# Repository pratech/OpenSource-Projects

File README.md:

# OpenSource-Projects
Open Source Pinwheel Robotics Project
Pinwheel Robotics is a company based in Bengaluru , Karnataka ,India
Our aim is to make programming and Robotics fun for students 
This will foster more creativity among kids.
At Pinwheel we believe Education should have no boundary and hence creating this open source projects hub.
Please contact us at admin@pinwheel.in
Alternate Email address of founder - prateek.ideafires@gmail.com
Our Tech blogs are at www.pinwheel.in
Facebook- www.facebook.com/pinwheeler
Instagram- www.instagram.com/pinwheelrobotics
Youtube - Search for Pinwheel Robotics .

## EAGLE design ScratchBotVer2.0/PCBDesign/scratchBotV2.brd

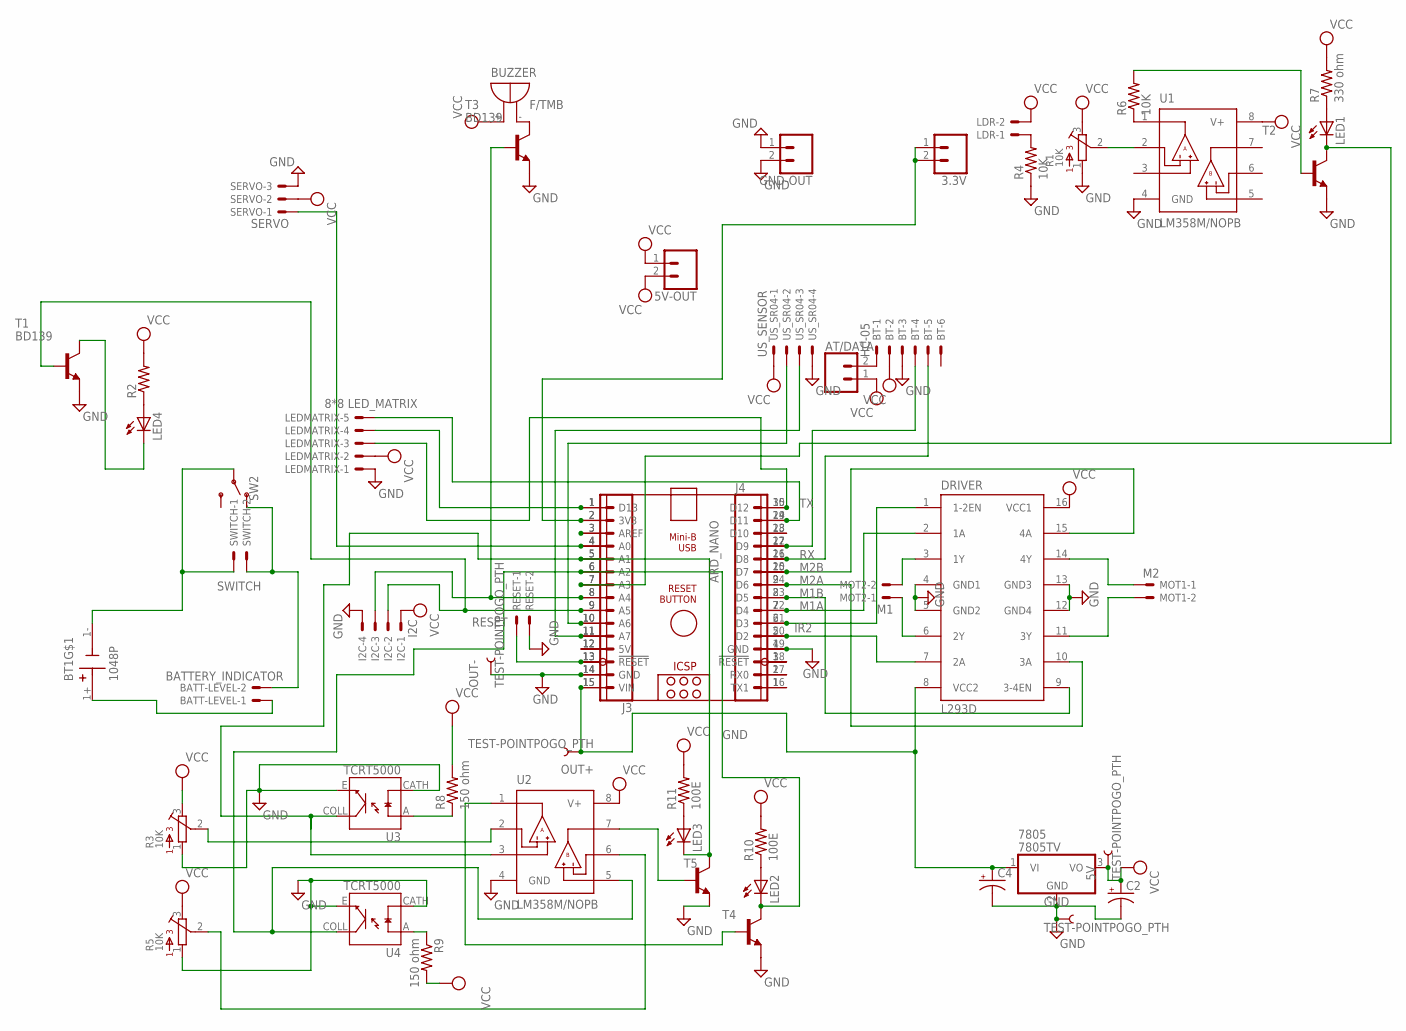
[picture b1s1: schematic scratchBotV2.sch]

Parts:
3.3V, 5V-OUT: CONN_02; 1X02
5V: TEST-POINTPOGO_PTH; 1X01_NO_SILK
7805: 7805TV; TO220V
ARD_NANO: ARDUINO_NANO
AT/DATA: CONN_02; 1X02
BATT-LEVEL: BATTERY_INDICATOR; JST-XH-02-PACKAGE-LONG-PAD
BT: HC-05; JST-XH-06-PACKAGE-LONG-PAD
BT1: 1048P; BAT_1048P
BUZZER: F/TMB
C2, C4: CPOL-USE2.5-5; E2,5-5
DRIVER: L293D; DIL16
GND: TEST-POINTPOGO_PTH; 1X01_NO_SILK
GND-OUT: CONN_02; 1X02
I2C: I2C; JST-XH-04-PACKAGE-LONG-PAD
J3, J4: CONN_15; 1X15
LDR: JST-XH-02-PIN-LONG-PAD; JST-XH-02-PACKAGE-LONG-PAD
LED1, LED2, LED3, LED4: LEDCHIPLED_1206; CHIPLED_1206
LEDMATRIX: 8*8 LED_MATRIX; JST-XH-05-PACKAGE-LONG-PAD
MOT1: M2; JST-XH-02-PACKAGE-LONG-PAD
MOT2: M1; JST-XH-02-PACKAGE-LONG-PAD
OUT+: TEST-POINTPOGO_PTH; 1X01_NO_SILK
OUT-: TEST-POINTPOGO_PTH; 1X01_NO_SILK
R1, R3, R5: 10K; 3362H
R2: R-US_0204/7; 0204/7
R4, R6: 10K; M1206
R7: 330 ohm; M1206
R8, R9: 150 ohm; M1206
R10, R11: 100E; M1206
RESET: RESET; JST-XH-02-PACKAGE-LONG-PAD
SERVO: SERVO; JST-XH-03-PACKAGE-LONG-PAD
SW2: SWITCH-SPDT-PTH-11.6X4.0MM; SWITCH_SPDT_PTH_11.6X4.0MM
SWITCH: SWITCH; JST-XH-02-PACKAGE-LONG-PAD
T1, T3: BD139; TO126
T2, T4, T5: -NPN-SOT23-EBC; SOT23-EBC
U1, U2: LM358M/NOPB; SOIC127P599X175-8N
U3, U4: TCRT5000; OPTO_TCRT5000
US_SR04: US_SENSOR; JST-XH-04-PACKAGE-LONG-PAD

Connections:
9V-MT3608: 7805.1 (VI), ARD_NANO.15 (VIN), C4.+, DRIVER.8 (VCC2), J3.15, OUT+.1
ECHO: ARD_NANO.8 (A4), I2C.3, J3.8, T3.3 (B)
GND: 7805.2 (GND), ARD_NANO.14 (GND), ARD_NANO.19 (GND), BT.3, C2.-, C4.-, DRIVER.4 (GND1), DRIVER.5 (GND2), DRIVER.12 (GND4), DRIVER.13 (GND3), GND.1, GND-OUT.1, GND-OUT.2, I2C.4, J3.14, J4.4, LEDMATRIX.1, OUT-.1, R1.1, R3.1, R4.1, R5.1, RESET.2, SERVO.3, T1.1 (E), T2.E, T3.1 (E), T4.E, T5.E, U1.4 (GND), U2.4 (GND), U3.CATH, U3.E, U4.CATH, U4.E, US_SR04.4
IR2: ARD_NANO.21 (D3), DRIVER.1 (1-2EN), J4.6
M1A: ARD_NANO.22 (D4), DRIVER.2 (1A), J4.7
M1B: ARD_NANO.23 (D5), DRIVER.9 (3-4EN), J4.8
M2A: ARD_NANO.24 (D6), DRIVER.10 (3A), J4.9
M2B: ARD_NANO.25 (D7), DRIVER.15 (4A), J4.10
unnamed: BT1.1-, SW2.2, SWITCH.1
unnamed: DRIVER.3 (1Y), MOT2.2
unnamed: R1.2, U1.2 (-INA)
unnamed: DRIVER.6 (2Y), MOT2.1
unnamed: ARD_NANO.4 (A0), J3.4, SERVO.1
unnamed: BATT-LEVEL.1, BT1.1+
unnamed: ARD_NANO.10 (A6), J3.10, US_SR04.2
unnamed: DRIVER.14 (4Y), MOT1.1
unnamed: ARD_NANO.28 (D10), J4.13
unnamed: DRIVER.11 (3Y), MOT1.2
unnamed: ARD_NANO.27 (D9), BT.4, J4.12
unnamed: ARD_NANO.1 (D13), J3.1, LEDMATRIX.4
unnamed: ARD_NANO.7 (A3), J3.7, LED1.C, T2.C
unnamed: ARD_NANO.5 (A1), J3.5, LED3.C, T5.C, U2.3 (+INA), U3.COLL
unnamed: LED4.C, T1.2 (C)
unnamed: BATT-LEVEL.2, SW2.1 (O), SWITCH.2
unnamed: ARD_NANO.13 (!RESET), J3.13, RESET.1
unnamed: 3.3V.1, 3.3V.2, ARD_NANO.2 (3V3), J3.2
unnamed: ARD_NANO.11 (A7), J3.11, US_SR04.3
unnamed: ARD_NANO.3 (AREF), J3.3
unnamed: ARD_NANO.9 (A5), I2C.2, J3.9, T1.3 (B)
unnamed: R8.1, U3.A
unnamed: ARD_NANO.12 (5V), J3.12
unnamed: LDR.1, R4.2
unnamed: R6.1, U1.1 (OUTA)
unnamed: R9.1, U4.A
unnamed: BUZZER.-, T3.2 (C)
unnamed: R6.2, T2.B
unnamed: ARD_NANO.6 (A2), J3.6, LED2.C, T4.C, U2.5 (+INB), U4.COLL
unnamed: ARD_NANO.29 (D11), J4.14, LEDMATRIX.5
unnamed: ARD_NANO.16 (TX1), J4.1
unnamed: ARD_NANO.17 (RX0), J4.2
unnamed: ARD_NANO.18 (!RESET), J4.3
unnamed: AT/DATA.2, BT.1
unnamed: LED1.A, R7.1
unnamed: ARD_NANO.20 (D2), DRIVER.7 (2A), J4.5
unnamed: R3.2, U2.2 (-INA)
unnamed: LED3.A, R11.1
unnamed: LED2.A, R10.1
unnamed: T4.B, U2.1 (OUTA)
unnamed: T5.B, U2.7 (OUTB)
unnamed: R5.2, U2.6 (-INB)
unnamed: LED4.A, R2.1
RX: ARD_NANO.26 (D8), BT.5, J4.11
TX: ARD_NANO.30 (D12), J4.15, LEDMATRIX.3
VCC: 5V.1, 5V-OUT.1, 5V-OUT.2, 7805.3 (VO), AT/DATA.1, BT.2, BUZZER.+, C2.+, DRIVER.16 (VCC1), I2C.1, LDR.2, LEDMATRIX.2, R1.3, R2.2, R3.3, R5.3, R7.2, R8.2, R9.2, R10.2, R11.2, SERVO.2, U1.8 (V+), U2.8 (V+), US_SR04.1

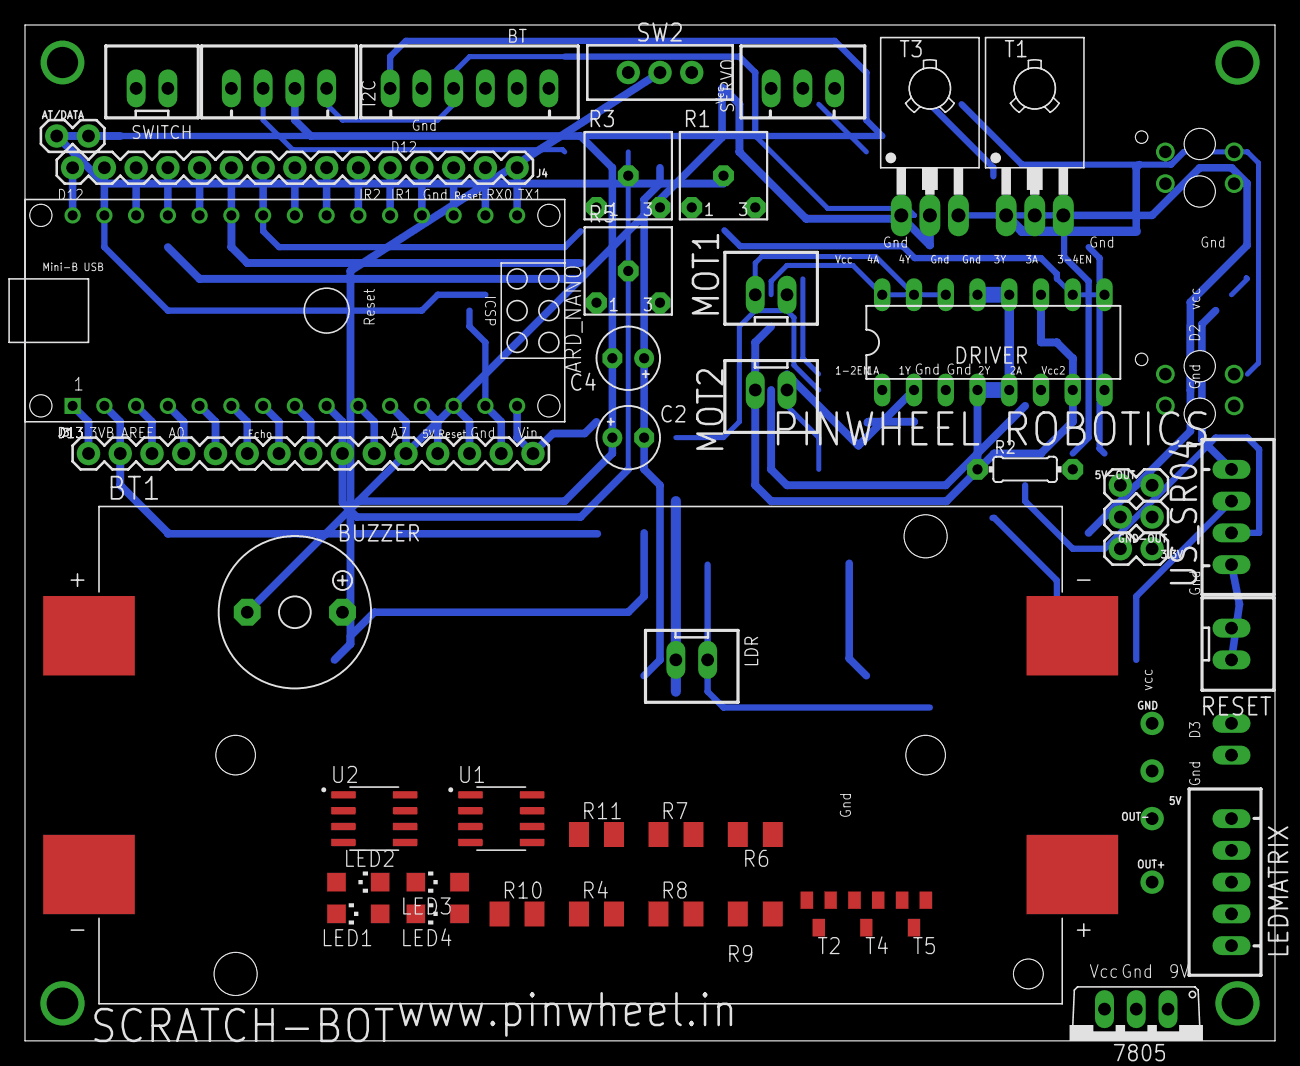
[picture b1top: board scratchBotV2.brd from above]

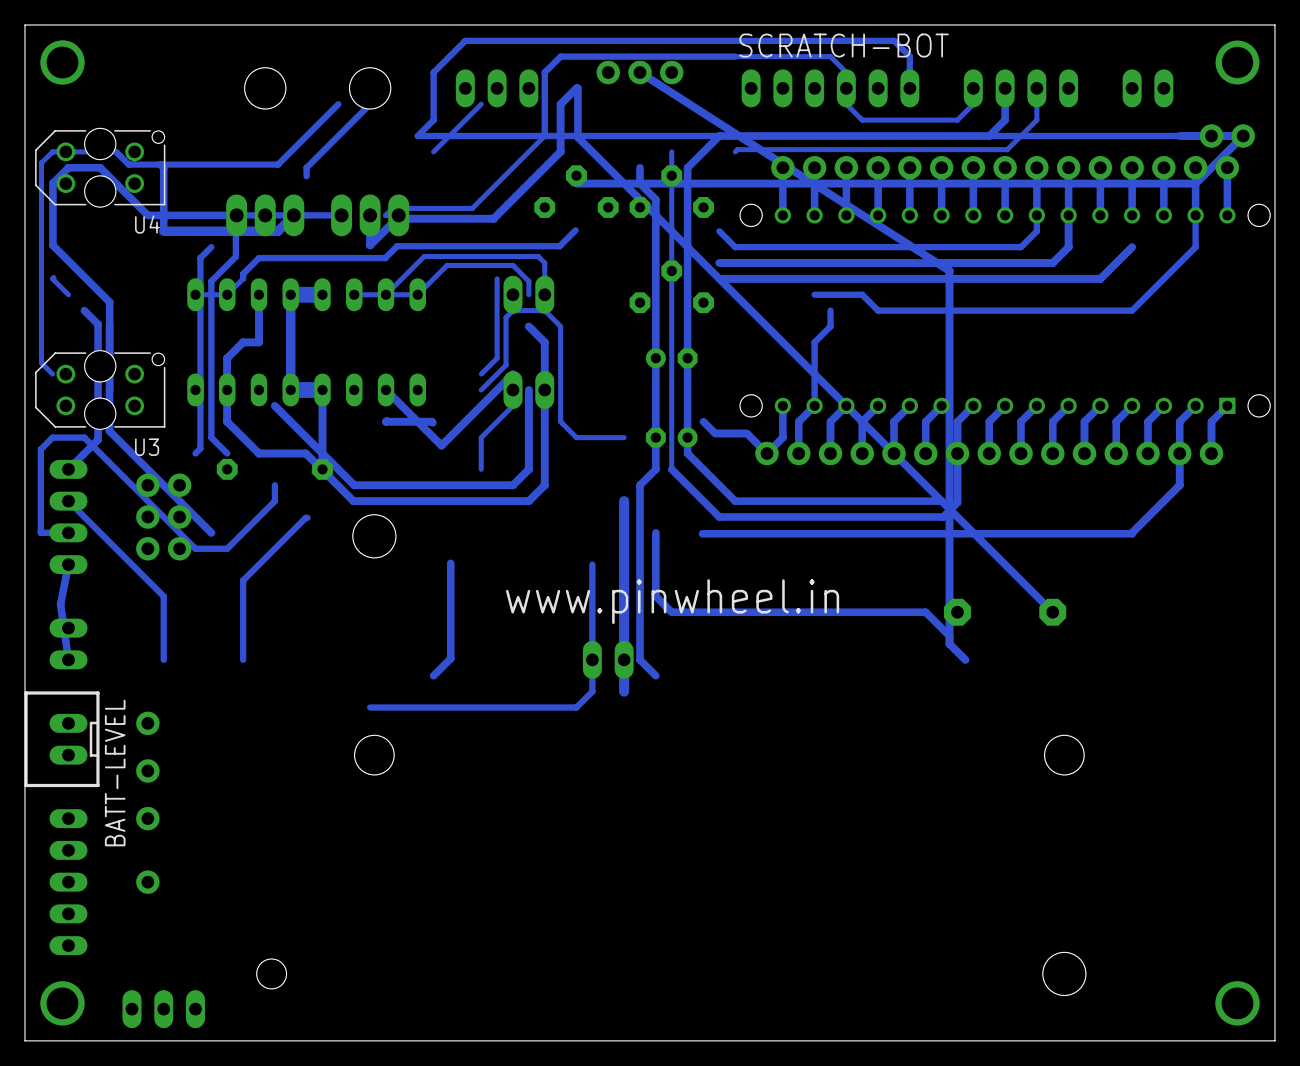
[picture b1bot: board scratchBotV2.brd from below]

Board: 2 copper layers, 100.0 x 81.3 mm, 53 parts (3 on the bottom side), 54 nets.

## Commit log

2021-08-03 updated schematic- added a transistor
2021-08-13 Adding Initial Commit
2021-08-13 InitialCommit
2021-08-13 moving and adding
2021-08-15 added base mount plate for motor gun
2021-08-15 some updates
2021-08-17 Moving to this location
2021-08-26 updated 90- deg upright notches
2021-09-03 lI ION BATTERY ADDED AND REVIEW OF OTHER COMPONENTS.
2021-09-03 Li ion battery added and review of other components mentioned in the FRD
2021-09-05 updated pin number
2021-09-07 Two TCR5000 circuit added for line follower.
2021-09-08 Output Pins of TCR5000 and LDR is connected to the analog pin of Arduino and reviewed the circuit.
2021-09-08 updated the FRD_ScratchBotV2.docx
2021-09-13 Resistors value updated
2021-10-04 component placement
2021-11-27 updatews
2021-11-27 Adding Images
2024-10-04 Starting new project on steering mech car assembly.
2024-11-13 Adding First Version of 5 IR Sensor Based Line Follower Sensor Code.

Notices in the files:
parts and their libraries:
SparkFun-Switches: Licensing: Creative Commons ShareAlike 4.0 International - https://creativecommons.org/licenses/by-sa/4.0
